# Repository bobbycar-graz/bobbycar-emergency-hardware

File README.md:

# bobbycar-emergency-hardware
This is a little project to control the bobbycar with only one analog stick for emergencies (for example main board-computer/steering wheel failure)

# Screenshot

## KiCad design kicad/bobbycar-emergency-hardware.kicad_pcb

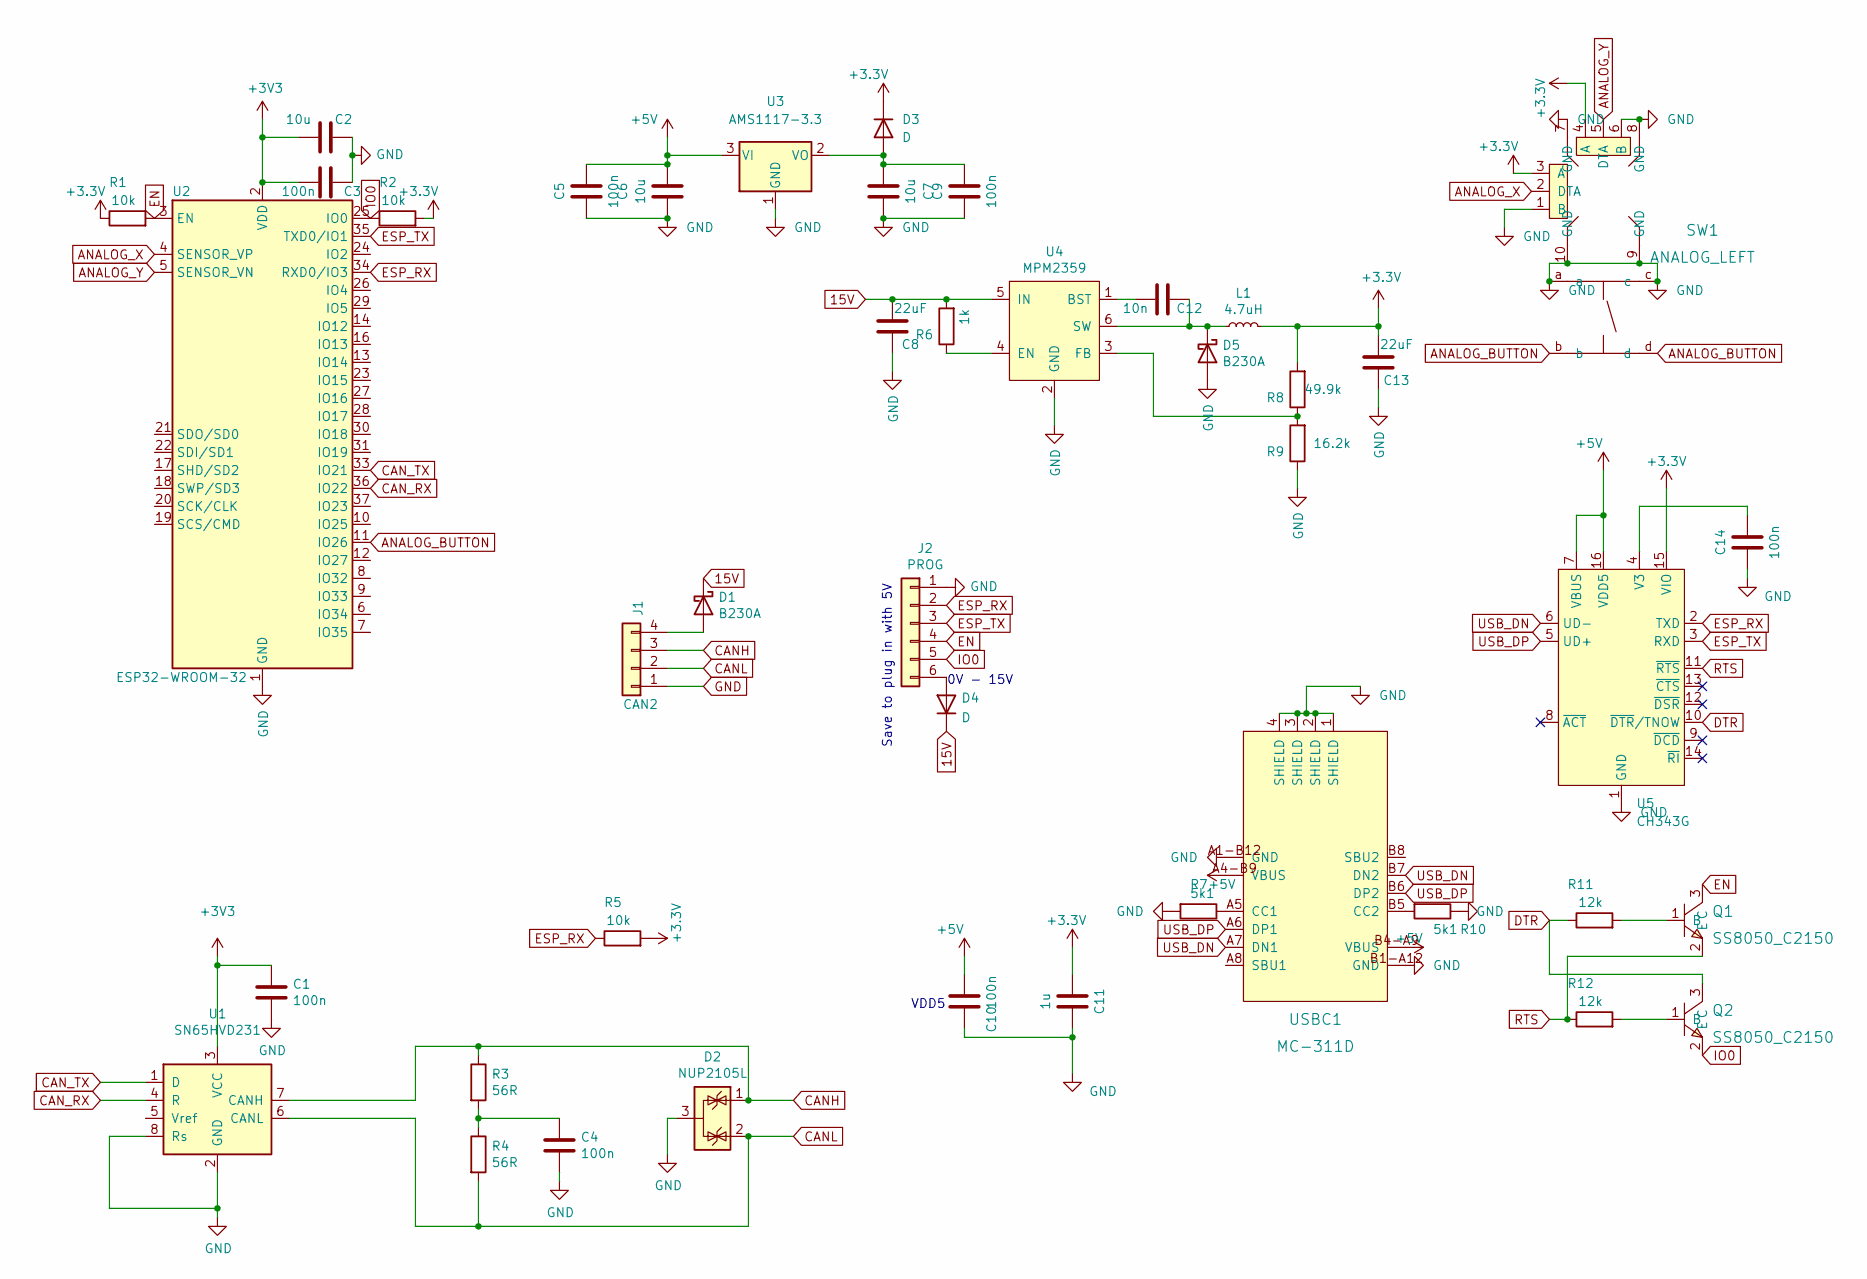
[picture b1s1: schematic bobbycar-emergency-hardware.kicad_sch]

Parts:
C1, C3, C4, C5, C9, C10, C14: 100n; C_0603_1608Metric; LCSC Part # C14663
C2, C6, C7: 10u; C_0603_1608Metric; LCSC Part # C19702
C8, C13: 22uF; C_0805_2012Metric; LCSC Part # C32375
C11: 1u; C_0603_1608Metric; LCSC Part # C15849
C12: 10n; C_0603_1608Metric; LCSC Part # C57112
D1, D5: B230A; D_SMA; LCSC Part # C12889
D2: NUP2105L; SOT-23; LCSC Part # C284104
D3, D4: D; D_SOD-123; LCSC Part # C8598
J1: CAN2; JST_XH_B4B-XH-A_1x04_P2.50mm_Vertical; LCSC Part # C144395
J2: PROG; JST_XH_B6B-XH-A_1x06_P2.50mm_Vertical; LCSC Part # C144397
L1: 4.7uH; L_5040; LCSC Part # C354606
Q1, Q2: SS8050_C2150; SOT-23-3_L2.9-W1.3-P1.90-LS2.4-BR; LCSC Part C2150
R1, R2, R5: 10k; R_0603_1608Metric; LCSC C25804
R3, R4: 56R; R_0603_1608Metric; LCSC Part # C25196
R6: 1k; R_0603_1608Metric; LCSC Part # C21190
R7, R10: 5k1; R_0603_1608Metric; LCSC C23186
R8: 49.9k; R_0603_1608Metric; LCSC Part # C23184
R9: 16.2k; R_0603_1608Metric; LCSC Part # C22885
R11, R12: 12k; R_0603_1608Metric; LCSC C22790
SW1: ANALOG_LEFT; SW-TH_RKJXV122400D; LCSC Part C2687349
U1: SN65HVD231; SOIC-8_3.9x4.9mm_P1.27mm; LCSC Part # C30530
U2: ESP32-WROOM-32; LCSC Part # C701342
U3: AMS1117-3.3; SOT-223-3_TabPin2; LCSC C6186
U4: MPM2359; SOT-23-6; LCSC Part # C2959845
U5: CH343G; SOIC-16_3.9x9.9mm_P1.27mm; LCSC C2844153
USBC1: MC-311D; USB-C-SMD_MC-311D; LCSC Part C136423

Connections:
15V: C8.2, D1.1 (K), D4.1 (K), R6.2, U4.5 (IN)
+5V: C5.2, C6.2, C10.2, U3.3 (VI), U5.7 (VBUS), U5.16 (VDD5), USBC1.A4-B9 (VBUS), USBC1.B4-A9 (VBUS)
ANALOG_BUTTON: SW1.b, SW1.d, U2.11 (IO26)
ANALOG_X: SW1.2 (DTA), U2.4 (SENSOR_VP)
ANALOG_Y: SW1.5 (DTA), U2.5 (SENSOR_VN)
CANH: D2.1 (K), J1.3, R3.1, U1.7 (CANH)
CANL: D2.2 (K), J1.2, R4.2, U1.6 (CANL)
CAN_RX: U1.4 (R), U2.36 (IO22)
CAN_TX: U1.1 (D), U2.33 (IO21)
DTR: Q2.3 (C), R11.1, U5.10 (~DTR/TNOW)
EN: J2.4, Q1.3 (C), R1.2, U2.3 (EN)
ESP_RX: J2.2, R5.1, U2.34 (RXD0/IO3), U5.2 (TXD)
ESP_TX: J2.3, U2.35 (TXD0/IO1), U5.3 (RXD)
GND: C1.2, C2.1, C3.1, C4.2, C5.1, C6.1, C7.2, C8.1, C9.1, C10.1, C11.1, C13.1, C14.1, D2.3 (A), D5.2 (A), J1.1, J2.1, R7.2, R9.1, R10.1, SW1.1 (B), SW1.6 (B), SW1.7 (GND), SW1.8 (GND), SW1.9 (GND), SW1.10 (GND), SW1.a, SW1.c, U1.2 (GND), U1.8 (Rs), U2.1 (GND), U2.15 (GND), U2.38 (GND), U2.39 (GND), U3.1 (GND), U4.2 (GND), U5.1 (GND), USBC1.1 (SHIELD), USBC1.2 (SHIELD), USBC1.3 (SHIELD), USBC1.4 (SHIELD), USBC1.A1-B12 (GND), USBC1.B1-A12 (GND)
IO0: J2.5, Q2.2 (E), R2.1, U2.25 (IO0)
unnamed: C4.1, R3.2, R4.1
unnamed: C7.1, C9.2, D3.2 (A), U3.2 (VO)
unnamed: C12.1, D5.1 (K), L1.1, U4.6 (SW)
unnamed: C12.2, U4.1 (BST)
unnamed: C14.2, U5.4 (V3)
unnamed: D1.2 (A), J1.4
unnamed: D4.2 (A), J2.6
unnamed: Q1.1 (B), R11.2
unnamed: Q2.1 (B), R12.2
unnamed: R6.1, U4.4 (EN)
unnamed: R7.1, USBC1.A5 (CC1)
unnamed: R8.1, R9.2, U4.3 (FB)
unnamed: R10.2, USBC1.B5 (CC2)
RTS: Q1.2 (E), R12.1, U5.11 (~RTS)
USB_DN: U5.6 (UD-), USBC1.A7 (DN1), USBC1.B7 (DN2)
USB_DP: U5.5 (UD+), USBC1.A6 (DP1), USBC1.B6 (DP2)

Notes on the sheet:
VDD5
Save to plug in with 5V
0V - 15V

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
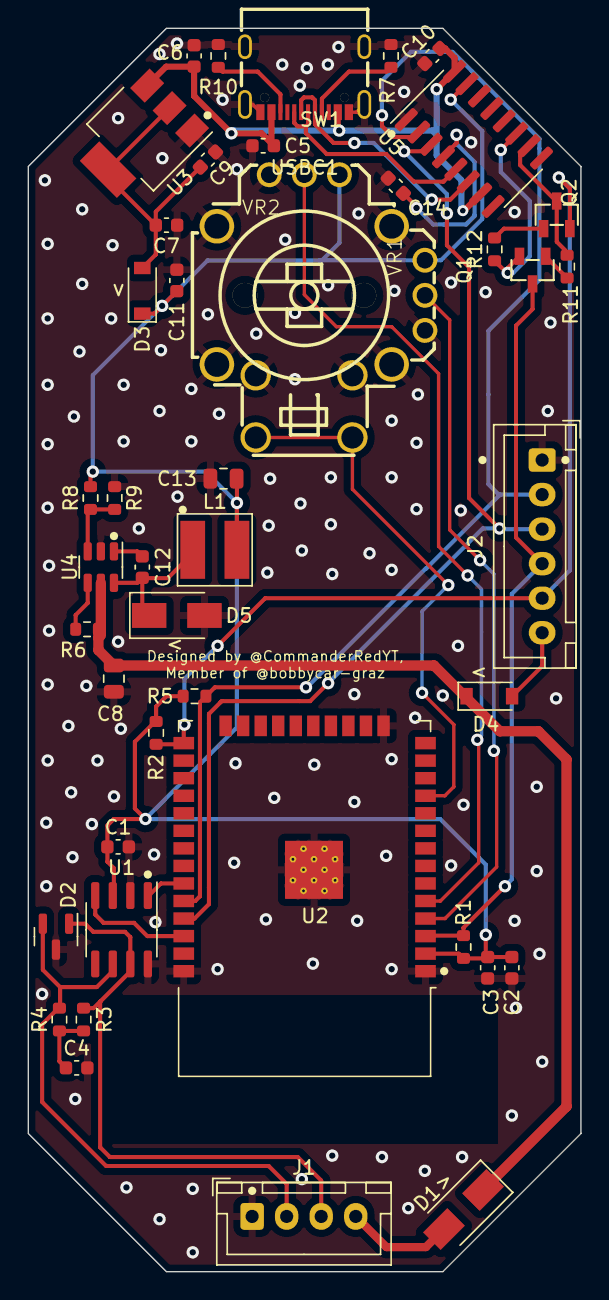
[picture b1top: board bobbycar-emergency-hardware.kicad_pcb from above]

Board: 2 copper layers, 40.0 x 90.0 mm, 43 parts (0 on the bottom side), 32 nets.

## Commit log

2022-10-07 KiCAD gitignore
2022-10-07 Added image and README.md
2022-10-07 PCB Files and more screenshots
2022-10-07 Fixed JLCPCB, added marks for orientation etc
